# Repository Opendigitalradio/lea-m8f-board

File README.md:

This repository contains a KiCAD project for a Ettus USRP B200-compatible
GPSDO that uses the u-blox LEA-M8F module.

It requires a modified UHD, because the reference clock output of the LEA-M8F is
30.72MHz.

This design is published under a Creative Commons CC-BY-SA licence, see
LICENCE.txt for details.

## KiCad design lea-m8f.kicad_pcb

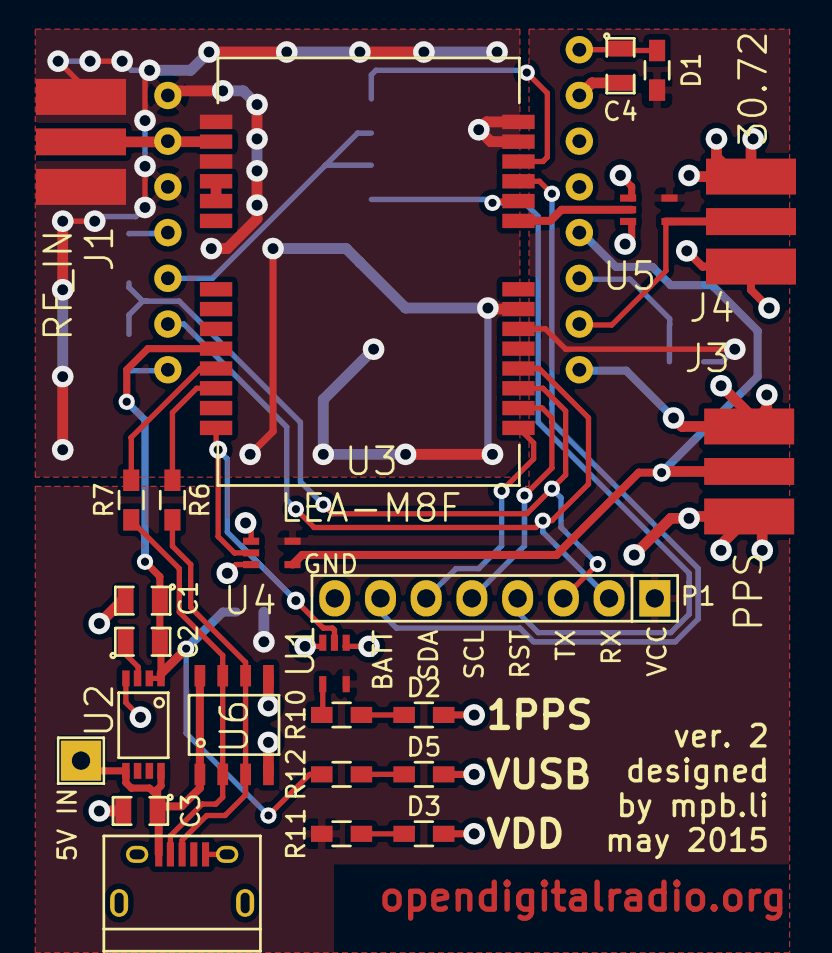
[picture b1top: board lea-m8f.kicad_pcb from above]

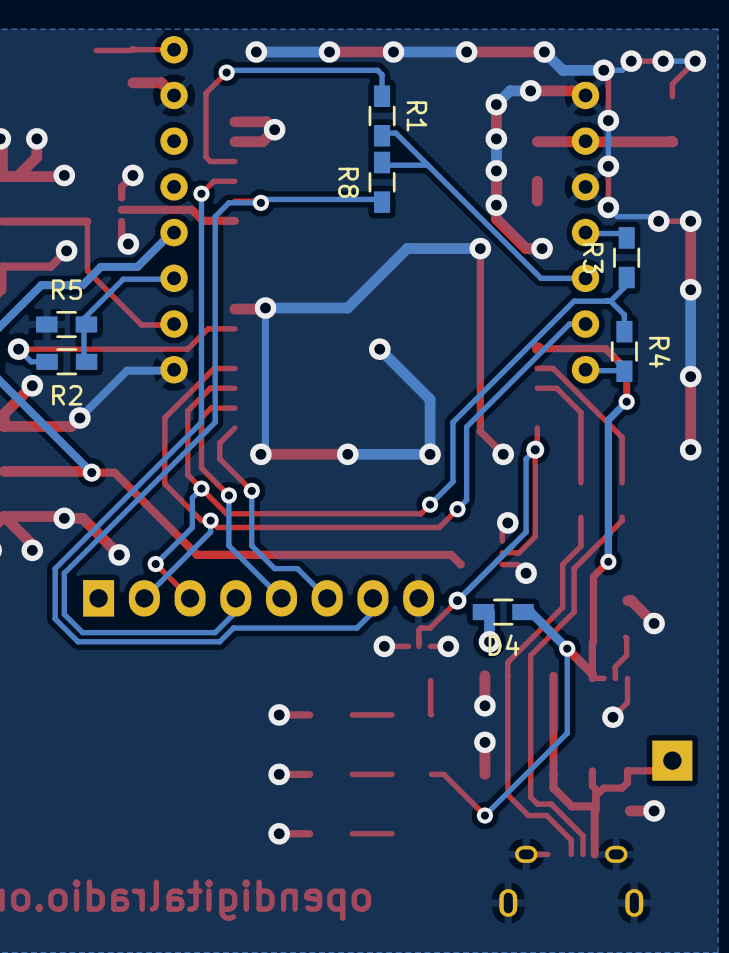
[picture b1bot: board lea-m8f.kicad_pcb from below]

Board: 2 copper layers, 33 parts (7 on the bottom side), 31 nets.

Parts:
C1: 10uF; SMD-0805
C2: 10nF; SMD-0805
C3, C4: 1uF; SMD-0805
CON1: USB-MICRO-B; USB_Micro-B
D1, D4: DIODESCH; R_0603_HandSoldering
D2: PPS; R_0603_HandSoldering
D3: VDD; R_0603_HandSoldering
D5: VUSB; R_0603_HandSoldering
J1: RF_IN; SMA_SIDE
J3: PPS; SMA_SIDE
J4: 30.72; SMA_SIDE
P1: CONN_01X08; Pin_Header_Straight_1x08
P2: 5V IN; Pin_Header_Straight_1x01
R1, R5, R8: DNF; R_0603_HandSoldering
R2, R3, R4: 0; R_0603_HandSoldering
R6, R7: 27; R_0603_HandSoldering
R10, R11, R12: 510; R_0603_HandSoldering
U1, U4, U5: NC7SZ125; SC70
U2: LT1962; MS8
U3: LEA-M8F; LEA
U6: USB6B1; SO-8
U100: B200_GPSDO; GPSDO_B200

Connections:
/5VUSB: C3.1, CON1.1, P2.1, U2.5, U2.8, U6.1, U6.8
/ISP_N: R1.2, R8.2, U100.13
/LOCK: R2.1, R5.2, U100.3
/M8F_PPS: U1.2, U3.28, U4.2
/PPS_BUFF: J3.2, U4.4, U100.4
/REFCLK: U3.9, U5.2
/REFCLK_BUFF: J4.2, U5.4, U100.2
/RESET_N: P1.4, R8.1, U3.10
/RF_IN: J1.2, U3.16, U100.10
/RXD: P1.2, U3.4, U100.14
/SB_N: R1.1, U3.12
/SCL: P1.5, U3.2
/SDA: P1.6, U3.1
/TXD: P1.3, R3.1, R4.1, U3.3
/VANT: U3.18, U3.19
/VBKP: P1.7, U3.11
/VDDUSB: C1.1, C2.2, D4.1, R12.1, U2.1, U2.2, U3.24
/VDD_B200: C4.1, D1.1, U100.8
GND: C1.2, C3.2, C4.2, CON1.5, CON1.6, CON1.7, CON1.8, CON1.9, D2.2, D3.2, D5.2, J1.1, J1.3, J3.1, J3.3, J4.1, J4.3, P1.8, R5.1, U1.1, U1.3, U2.4, U3.7, U3.13, U3.14, U3.15, U3.17, U4.1, U4.3, U5.1, U5.3, U6.4, U6.5, U100.1, U100.7, U100.9, U100.11
unnamed: C2.1, U2.3
unnamed: CON1.2, R7.1, U6.2, U6.7
unnamed: CON1.3, R6.1, U6.3, U6.6
unnamed: D2.1, R10.2
unnamed: D3.1, R11.1
unnamed: D5.1, R12.2
unnamed: R3.2, U100.12
unnamed: R4.2, U100.15
unnamed: R6.2, U3.26
unnamed: R7.2, U3.25
unnamed: R10.1, U1.4
VCC: D1.2, D4.2, P1.1, R2.2, R11.2, U1.5, U3.6, U4.5, U5.5

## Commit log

2014-12-20 Create lib and add footprint for LEA-M8F
2014-12-22 Add footprints and corrections
2014-12-22 Add components to board
2014-12-22 Add datasheets
2015-01-09 Start place and route
2015-01-10 More routing
2015-01-10 Check what happens with polygon pours
2015-01-11 do zone via stitch, correct footprints, revise board outline
2015-01-11 Correct margin on the left
2015-01-23 update PCB
2015-01-23 Remove UART connector and max232
2015-01-23 update schematic
    add LEDs for power and PPS
    correct power managment (diodes)
2015-01-23 Annotate schematic
2015-01-23 Add text to PCB
2015-01-23 Correct LEA footprint, add silkscreen
2015-01-23 Fixed footprints and layout
2015-01-23 Add manufacturing outputs
2015-01-23 add gerber renamer script
2015-02-13 Put GND below LEA
2015-02-13 Update footprints
2015-02-14 Add README
2015-02-14 Add LICENCE
2015-02-14 Add more GND vias and move some tracks
2015-05-14 Rename lea-m8f.zip
2015-05-14 Some corrections, and change date on silkscreen
2015-05-14 Add production files for may 2015 run
2015-10-27 Update footprint for diodes
2016-06-16 Add comments to schematic and 3V3 LDO
